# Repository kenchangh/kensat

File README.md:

# KENSAT — Edge-AI Compute in Orbit

> A 2U CubeSat that runs a large language model on-orbit. A power-gated NVIDIA
> Jetson Orin Nano executes neural-network inference in space, and the results
> are downlinked over a custom UHF radio link to amateur ground stations.

KENSAT's mission is to demonstrate **autonomous AI compute on a small
satellite** — taking a GPU-class accelerator and a quantized LLM out of the
data center and running them inside the tight power, thermal, and reliability
envelope of a 2U CubeSat. The on-board computer wakes the Jetson only when
needed, runs an inference within a measured energy budget, and frames the
output for downlink. Everything else in the spacecraft — the flight software,
the UHF radio and its RF matching networks, the power system, and the
antenna-deployment hardware — exists to get that compute on orbit, keep it
alive, and get its results to the ground.

**Why it's hard.** Edge AI in orbit means treating a multi-watt accelerator as
a scheduled, fault-tolerant *load*: powering it from a battery-backed bus only
in defined windows, dissipating its heat passively in vacuum, recovering it if
it hangs, and surviving the brownouts and resets that come with switching that
much current on a small satellite. KENSAT is built end to end around that
problem.

**Mission profile:** a 520 km sun-synchronous orbit, operating UHF amateur
radio at **437.08 MHz** for beaconing, telemetry downlink, and command uplink.
Telemetry — including downlinked inference results — is intentionally
**unencrypted** so amateur operators worldwide can receive and decode it.

---

## Radio link (for receiving stations)

KENSAT beacons openly on the UHF amateur band — no encryption, no keys.
Anyone with a 70 cm receiver and a G3RUH-capable TNC (Direwolf, gr-satellites,
SatNOGS) can decode it.

| | |
|---|---|
| **Beacon / downlink frequency** | **437.080 MHz** |
| **Transmitter** | Mode U — GFSK 1k2 AX.25 G3RUH |
| **Modulation** | GFSK |
| **Baud** | 1200 |
| **Framing** | AX.25 UI, NRZI + G3RUH |
| **Source callsign** | KO6IKZ |
| **Beacon interval** | ~10 s |
| **Status** | active |
| **Encryption** | none — telemetry is open by design |

Everything in the info field is plain ASCII. Frames are identified by their
first token:

| Frame | Carries |
|-------|---------|
| `BCN` | Housekeeping beacon: cumulative sequence number, boot count, reset cause, uptime, body rates, uplink frames received |
| `LLM` | One per on-orbit inference: Jetson temperatures and peaks, power, RAM, model-load and inference times, result CRC-32, and how many text frames to expect |
| `TXT` | The text the on-board LLM generated, as numbered chunks — `s=` result, `c=<k>/<m>` chunk, `h=` CRC-32 of the whole result |
| `ACK` | Acknowledgement of a received telecommand |

A result is sent one chunk per beacon cycle and the whole set twice, because
the link has no ARQ. To reassemble: group by `s=`, order by `c=`, concatenate,
and check `h=` (standard CRC-32). `ground-station/llm_downlink.py` does this
for you, from live decoder output or a saved log.

Command uplink is a short authenticated ASCII telecommand (Si4463 native
framing, CRC-16) that can inhibit the transmitter, ping the spacecraft, uplink
a prompt of up to 256 characters for the LLM in a single frame (which starts
the inference), or run a library prompt. Formats, verbs and the
reasoning behind them are in
**[firmware/obc/README.md](firmware/obc/README.md#the-radio-link)**.

Decoders, the result reassembler and an end-to-end test harness live in
**[ground-station](ground-station)**.

---

## System at a glance

```
        ┌──────────────────────────────────────────────┐
        │  Burn-Wire Board (custom)                     │  Slot 4 (top)
        │  Antenna-release driver · resistive heating   │
        ├──────────────────────────────────────────────┤
        │  Radio Board (custom)                         │  Slot 3
        │  Si4463 UHF transceiver + AS179 T/R switch    │
        │  Jetson Orin Nano (edge-AI payload)           │
        ├──────────────────────────────────────────────┤
        │  EPS Board (custom)                           │  Slot 2
        │  2S2P 18650 pack · rails · hardware watchdog  │
        ├──────────────────────────────────────────────┤
        │  Pumpkin MB + PPM D1 (PIC24FJ256GB210)        │  Slot 1 (bottom)
        │  OBC — always-on C&DH, Salvo RTOS             │
        └──────────────────────────────────────────────┘
              104-pin CubeSat Kit Bus (H1/H2)

   UHF dipole ── U.FL ── matching network ── AS179 ── Si4463 ── SPI ── PIC24
```

Boards interconnect over the 104-pin CubeSat Kit Bus. The PIC24 is the
always-on flight computer; it talks to the EPS over I²C, drives the Si4463
radio over SPI, controls and exchanges data with the Jetson over UART, and
fires the antenna-deployment burn wires over GPIO.

See **[docs/system-architecture.md](docs/system-architecture.md)** for the full
spec: pinouts, bus map, operational modes, deployment state machine, power
budget, and thermal analysis.

---

## Subsystems

| Subsystem | What it is | Highlights |
|-----------|-----------|------------|
| **[firmware/obc](firmware/obc)** | PIC24 flight software (C, Salvo RTOS) | Fault-tolerant antenna deployment with flash-persisted state, AX.25 beacons, Si4463 driver, IMU, SD/serial-flash logging, command parser |
| **[radio](radio)** | Custom 437 MHz UHF radio board | Si4463 + AS179 T/R switch, ESP32-S3 firmware, KiCad 2-layer design |
| **[radio/rf-design](radio/rf-design)** | RF matching-network design & test | Custom scikit-rf optimizer over LCSC-stocked parts, CPWG parasitic modeling, ADALM-Pluto SDR test bench |
| **[eps](eps)** | Electrical power system board | 2S2P 18650 pack, regulated rails, hardware watchdog (KiCad) |
| **[burnwire](burnwire)** | Antenna-release deployment board | Redundant nichrome burn-wire driver (KiCad) |
| **[jetson](jetson)** | Edge-AI payload | Jetson Orin Nano running a quantized LLM (llama.cpp/TinyLlama) over UART, systemd daemons, thermal management |
| **[ground-station](ground-station)** | SDR ground station & decoders | ADALM-Pluto RX/TX, AX.25 beacon decoder, DSP diagnostics, end-to-end test harness |
| **[docs](docs)** | System documentation | Architecture spec, radio guide, Jetson startup, debug notes |

---

## Engineering highlights

- **An LLM running in orbit.** The payload is an NVIDIA Jetson Orin Nano running
  a quantized TinyLlama model under llama.cpp. The always-on PIC24 keeps it
  powered down, then — on schedule or command — switches on its rail through a
  high-side load switch, waits for the Jetson to boot and signal `READY` over
  UART, dispatches a prompt, collects the generated text, powers the Jetson back
  off, and queues the result for downlink. The whole cycle is bounded by a
  measured **per-inference energy budget** so a single run can't drain the pack.
  Prompts come either from a library pre-loaded on the payload — so the mission
  produces results with no uplink at all — or from the ground, uplinked as a
  single 256-byte prompt field that the OBC runs as soon as it arrives.
  ([docs/system-architecture.md §6.2](docs/system-architecture.md), [jetson/](jetson))

- **Treating a GPU as a spacecraft load.** Running multi-watt edge compute on a
  2U bus is a systems problem: the EPS sizes a battery-backed rail and a
  hardware watchdog around the Jetson's draw, the OBC power-gates it and can
  recover a hung payload by cutting power, and the design accounts for
  dissipating its heat **passively in vacuum**, where there's no convection.
  ([docs/system-architecture.md §8.1](docs/system-architecture.md))

- **Fault-tolerant by construction.** Both the inference cycle and the antenna
  burn-wire release are one-shot, flash-persisted state machines that survive
  the brownouts and resets that come with switching large currents: attempt
  counts are written *before* energizing, success flags only *after* completion,
  and the RF-silence hold fails *safe* toward staying quiet.
  ([details](docs/system-architecture.md))

- **A complete UHF link to get results down.** TX / RX / antenna matching
  networks were designed with a custom scikit-rf grid-search optimizer that
  models PCB traces as CPWG transmission lines (elliptic-integral method) and
  snaps to real LCSC part values, then validated on an ADALM-Pluto SDR loopback
  bench (gain sweep, harmonics, insertion loss). Inference output is framed as
  AX.25 and downlinked openly. ([radio/rf-design](radio/rf-design))

- **Signal-integrity-aware bus design.** The Si4463 SPI bus crosses two
  board-to-board connectors; the design derates the clock and adds series
  termination accordingly. ([docs/spi-debug-notes.md](docs/spi-debug-notes.md))

---

## Repository layout

```
kensat/
├── docs/             System architecture spec + guides
├── firmware/obc/     PIC24 flight software (app/ + bsp/)
├── radio/            UHF radio: ESP32 firmware, KiCad board, RF design
├── eps/              Electrical power system board (KiCad)
├── burnwire/         Antenna deployment board (KiCad)
├── jetson/           Edge-AI payload daemon + systemd units
└── ground-station/   SDR scripts, beacon decoder, diagnostics
```

## Building

- **OBC firmware** depends on proprietary vendor SDKs (Pumpkin CubeSat Kit BSP,
  Salvo RTOS) that are **not** redistributed here. See
  **[firmware/obc/BUILD.md](firmware/obc/BUILD.md)**.
- **Radio firmware** builds with arduino-cli for the ESP32-S3.
- **RF design / ground-station** tools are Python; see the `requirements.txt`
  in each directory.

## License

Original work in this repository is released under the [MIT License](LICENSE).
Proprietary vendor SDKs the firmware builds against are **not** included and are
**not** covered by that license — see the LICENSE file and
[firmware/obc/BUILD.md](firmware/obc/BUILD.md).

---

*KENSAT — UHF amateur satellite, 437.08 MHz. Telemetry is open and unencrypted
by design, in the tradition of the amateur radio community.*

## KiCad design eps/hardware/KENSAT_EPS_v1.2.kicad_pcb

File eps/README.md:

# Electrical Power System (EPS)

Custom EPS board for KENSAT — Slot 2 in the 2U stack, above the OBC. Generates and
distributes the satellite's power rails, manages the battery pack, and provides
a hardware watchdog that can power-cycle the rest of the spacecraft.

- **Battery:** 2S2P 18650 Li-ion pack (mounted on the board underside)
- **Rails:** regulated buses distributed over the 104-pin CubeSat Kit Bus
- **Telemetry:** battery voltage / current / temperature, read by the OBC over I²C
- **Reliability:** hardware watchdog (see
  [docs/system-architecture.md](../docs/system-architecture.md) §7.1)

## Files

```
eps/hardware/
├── KENSAT_EPS_v1.2.kicad_pro   KiCad project
├── KENSAT_EPS_v1.2.kicad_sch   Schematic
└── KENSAT_EPS_v1.2.kicad_pcb   PCB layout
```

Open with [KiCad](https://www.kicad.org/) 7+. Power-rail and bus pin
assignments are documented in
[docs/system-architecture.md](../docs/system-architecture.md) §5.6–5.7.

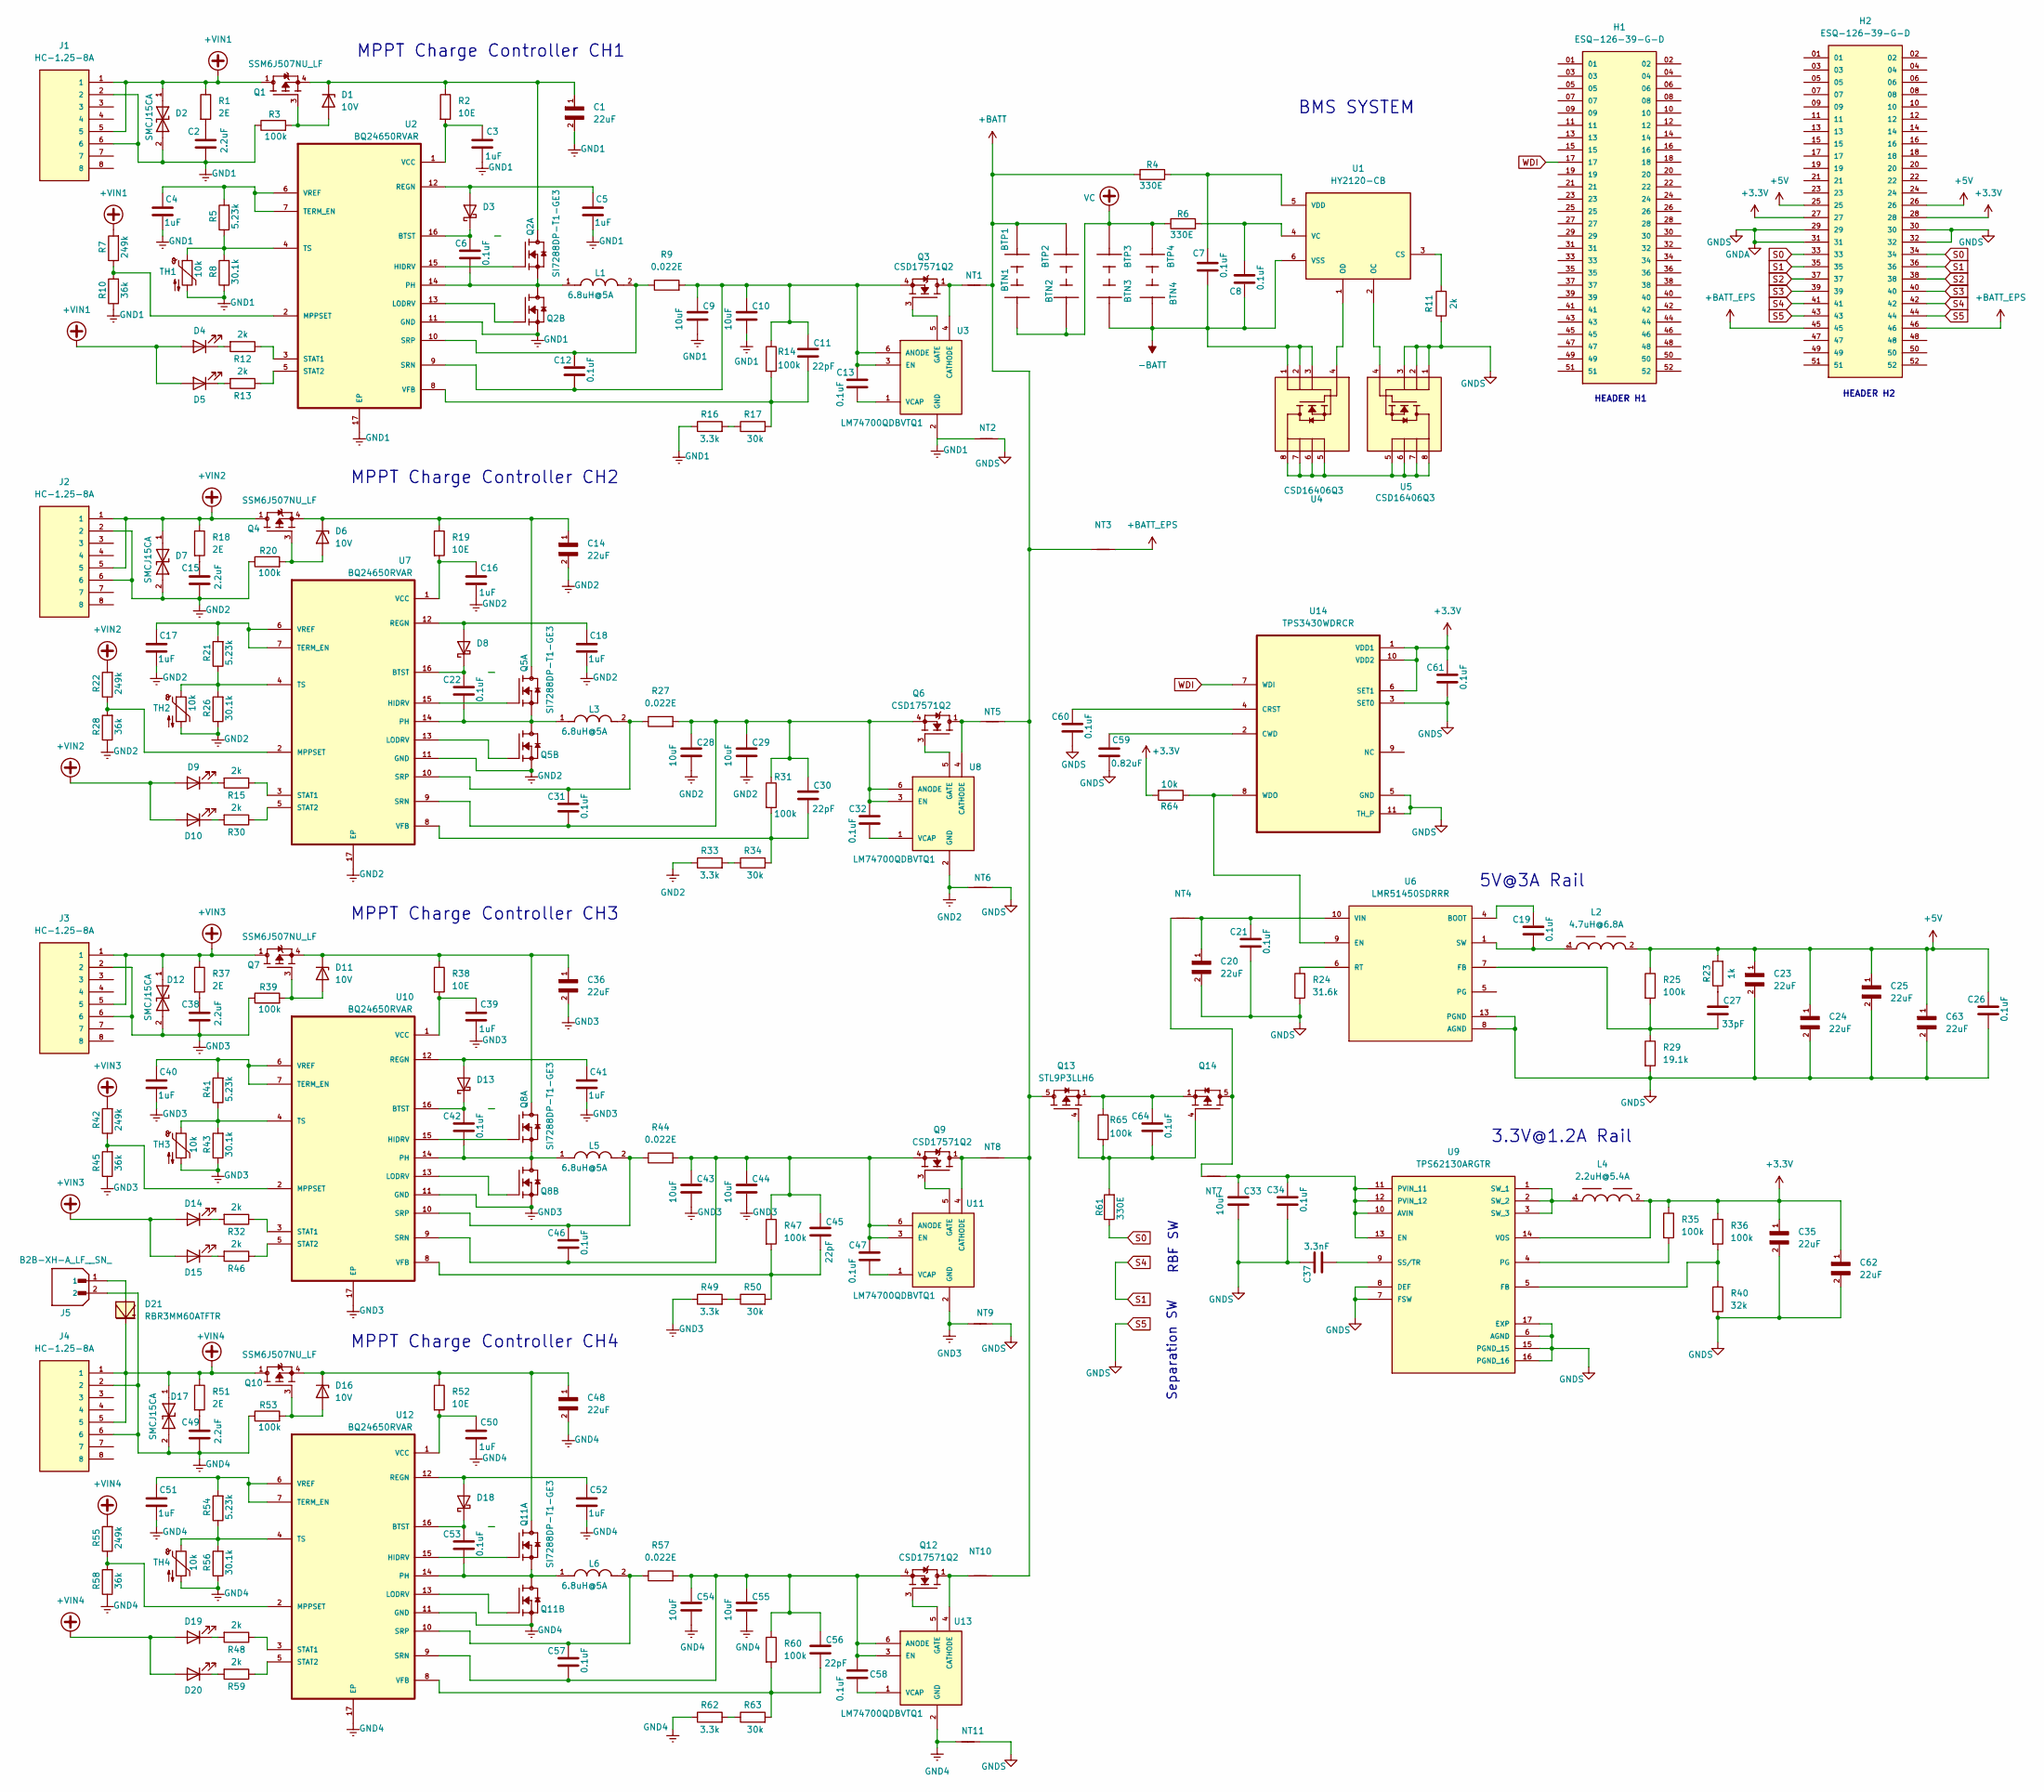
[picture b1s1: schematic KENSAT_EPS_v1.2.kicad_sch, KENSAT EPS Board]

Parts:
BTN1, BTN2, BTN3, BTN4: MY-18650-02; BAT_254TR; PARTREV C; LCSC Part C2979182
BTP1, BTP2, BTP3, BTP4: MY-18650-02; BAT_254TR; PARTREV C; LCSC Part C2979182
C1, C14, C20, C23, C24, C25, C35, C36, C48, C62, C63: 22uF; CAPC3225X270N; Voltage 35V; LCSC Part C386098
C2, C15, C38, C49: 2.2uF; C_1210_3225Metric; Voltage 100V; LCSC Part C92775
C3, C4, C5, C16, C17, C18, C39, C40, C41, C50, C51, C52: 1uF; C_0603_1608Metric; Voltage 35V; LCSC Part C841050
C6, C7, C8, C12, C13, C19, C21, C22, C26, C31, C32, C34, C42, C46, C47, C53, C57, C58, C60, C61, C64: 0.1uF; C_0603_1608Metric; Voltage 50V; LCSC Part C386155
C9, C10, C28, C29, C33, C43, C44, C54, C55: 10uF; C_1210_3225Metric; Voltage 35V; LCSC Part C2177081
C11, C30, C45, C56: 22pF; C_0603_1608Metric; Voltage 50V; LCSC Part C2169931
C27: 33pF; C_0603_1608Metric; Voltage 16V; LCSC Part C2169365
C37: 3.3nF; C_0603_1608Metric; Voltage 50V; LCSC Part C107088
C59: 0.82uF; C_0603_1608Metric; Voltage 25V; LCSC Part C5360807
D1, D6, D11, D16: 10V; D_SOD-123; LCSC Part C49435551
D2, D7, D12, D17: SMCJ15CA; DIOM7959X262N; PARTREV 11/20/15; LCSC Part C2842380
D3, D8, D13, D18: D_Schottky; D_SOD-323; LCSC Part C151503
D4, D9, D14, D19: LED; R_0603_1608Metric; LCSC Part C125099
D5, D10, D15, D20: LED; R_0603_1608Metric; LCSC Part C125093
D21: RBR3MM60ATFTR; SOD-123FL-2; LCSC Part C559758
H1, H2: ESQ-126-39-G-D; PARTREV R; LCSC Part C7466599
J1, J2, J3, J4: HC-1.25-8A; DF138P125DSA; MOUSER_PART_NUMBER 798-DF13-8P-1.25DSA
J5: B2B-XH-A_LF__SN_; JST_B2B-XH-A_LF__SN_; PARTREV N/A; LCSC Part C158012
L1, L3, L5, L6: 6.8uH@5A; INDDFN420X420X420-2N; PARTREV 09/15/2025; LCSC Part C52988778
L2: 4.7uH@6.8A; WE-XHMI_5030; LCSC Part C50326272
L4: 2.2uH@5.4A; WE-XHMI_5030; LCSC Part C48391578
NT1, NT2, NT3, NT4, NT5, NT6, NT7, NT8, NT9, NT10, NT11: NetTie_2; SolderJumper-2_P1.3mm_Bridged2Bar_Pad1.0x2.5mm
Q1, Q4, Q7, Q10: SSM6J507NU_LF; TRANS_SSM6J507NU_LF; PARTREV 2.0; LCSC Part C146318
Q2, Q5, Q8, Q11: SI7288DP-T1-GE3; TRANS_SI7288DP-T1-GE3; PARTREV A; LCSC Part C126988
Q3, Q6, Q9, Q12: CSD17571Q2; TRANS_CSD17571Q2; PARTREV A; LCSC Part C962382
Q13, Q14: STL9P3LLH6; TRANS_STL9P3LLH6; PARTREV 3; LCSC Part C2969828
R1, R18, R37, R51: 2E; R_2010_5025Metric; LCSC Part C2084800
R2, R19, R38, R52: 10E; R_1206_3216Metric; LCSC Part C304131
R3, R14, R20, R25, R31, R35, R36, R39, R47, R53, R60, R65: 100k; R_0603_1608Metric; LCSC Part C163504
R4, R6, R61: 330E; R_1206_3216Metric; LCSC Part C114944
R5, R21, R41, R54: 5.23k; R_0603_1608Metric; LCSC Part C185317
R7, R22, R42, R55: 249k; R_0603_1608Metric; LCSC Part C311921
R8, R26, R43, R56: 30.1k; R_0603_1608Metric; LCSC Part C137745
R9, R27, R44, R57: 0.022E; R_1206_3216Metric; LCSC Part C875620
R10, R28, R45, R58: 36k; R_0603_1608Metric; LCSC Part C311904
R11, R12, R13, R15, R30, R32, R46, R48, R59: 2k; R_0603_1608Metric; LCSC Part C105576
R16, R33, R49, R62: 3.3k; R_0603_1608Metric; LCSC Part C227493
R17, R34, R50, R63: 30k; R_0603_1608Metric; LCSC Part C700503
R23: 1k; R_1206_3216Metric; LCSC Part C131398
R24: 31.6k; R_0603_1608Metric; LCSC Part C185339
R29: 19.1k; R_0603_1608Metric; LCSC Part C173754
R40: 32k; R_0603_1608Metric; LCSC Part C861325
R64: 10k; R_0603_1608Metric; LCSC Part C98220
TH1, TH2, TH3, TH4: 10k; PinHeader_1x02_P2.00mm_Vertical; LCSC Part C7509625
U1: HY2120-CB; SOT-23-6; PARTREV 1.5_00; LCSC Part C116509
U2, U7, U10, U12: BQ24650RVAR; QFN50P350X350X100-17N; LCSC Part C53712
U3, U8, U11, U13: LM74700QDBVTQ1; SOT95P280X145-6N; PARTREV F; LCSC Part C2653623
U4, U5: CSD16406Q3; TRANS_CSD16406Q3; LCSC Part C2861720
U6: LMR51450SDRRR; CONV_LMR51450SDRRR; PARTREV December 2022; LCSC Part C6890985
U9: TPS62130ARGTR; QFN50P300X300X100-17N; PARTREV E; LCSC Part C337502
U14: TPS3430WDRCR; VREG_V62_16624-01YE; LCSC Part C2870545

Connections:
+3.3V: C35.1, C61.2, C62.1, H2.27, H2.28, L4.2, R35.1, R36.1, R64.2, U9.14 (VOS), U14.1 (VDD1), U14.6 (SET1), U14.10 (VDD2)
+5V: C23.1, C24.1, C25.1, C26.2, C63.1, H2.25, H2.26, L2.2, R23.2, R25.1
+BATT: BTP1.P1, BTP1.P2, BTP2.P1, BTP2.P2, NT1.2, NT3.1, NT5.2, NT8.2, NT10.2, Q13.5, Q13.5_1, Q13.5_2, R4.1
+BATT_EPS: H2.45, H2.46, NT3.2
+VIN1: D2.1, D4.2 (A), D5.2 (A), J1.1, J1.5, Q1.1, Q1.2, Q1.5, Q1.6, Q1.7, R1.1, R7.2
+VIN2: D7.1, D9.2 (A), D10.2 (A), J2.1, J2.5, Q4.1, Q4.2, Q4.5, Q4.6, Q4.7, R18.1, R22.2
+VIN3: D12.1, D14.2 (A), D15.2 (A), J3.1, J3.5, Q7.1, Q7.2, Q7.5, Q7.6, Q7.7, R37.1, R42.2
+VIN4: D17.1, D19.2 (A), D20.2 (A), D21.C, J4.1, J4.5, Q10.1, Q10.2, Q10.5, Q10.6, Q10.7, R51.1, R55.2
-BATT: BTN3.P1, BTN3.P2, BTN4.P1, BTN4.P2, C7.1, C8.1, U1.6 (VSS), U4.1, U4.2, U4.3
GND1: C1.2, C2.2, C3.2, C4.2, C5.2, C9.2, C10.2, D2.2, J1.2, J1.6, NT2.1, Q2.3, R3.1, R8.1, R10.1, R16.1, TH1.2, U2.11 (GND), U2.17 (EP), U3.2 (GND)
GND2: C14.2, C15.2, C16.2, C17.2, C18.2, C28.2, C29.2, D7.2, J2.2, J2.6, NT6.1, Q5.3, R20.1, R26.1, R28.1, R33.1, TH2.2, U7.11 (GND), U7.17 (EP), U8.2 (GND)
GND3: C36.2, C38.2, C39.2, C40.2, C41.2, C43.2, C44.2, D12.2, J3.2, J3.6, NT9.1, Q8.3, R39.1, R43.1, R45.1, R49.1, TH3.2, U10.11 (GND), U10.17 (EP), U11.2 (GND)
GND4: C48.2, C49.2, C50.2, C51.2, C52.2, C54.2, C55.2, D17.2, J4.2, J4.6, J5.2, NT11.1, Q11.3, R53.1, R56.1, R58.1, R62.1, TH4.2, U12.11 (GND), U12.17 (EP), U13.2 (GND)
unnamed: C2.1, R1.2
unnamed: C15.1, R18.2
unnamed: C19.1, L2.1, U6.1 (SW), U6.2 (SW), U6.3 (SW)
unnamed: C20.1, C21.2, NT4.2, U6.10 (VIN), U6.11 (VIN), U6.12 (VIN)
unnamed: C27.1, R23.1
unnamed: C38.1, R37.2
unnamed: C49.1, R51.2
unnamed: C64.1, Q13.4, Q14.4, R61.2, R65.2
unnamed: C64.2, Q13.1, Q13.2, Q13.3, Q14.1, Q14.2, Q14.3, R65.1
unnamed: D1.2 (A), Q1.3, R3.2
unnamed: C1.1, D1.1 (K), Q1.4, Q1.8, Q2.7_8_9, R2.1
unnamed: C5.1, D3.2 (A), U2.12 (REGN)
unnamed: C6.2, D3.1 (K), U2.16 (BTST)
unnamed: D4.1 (K), R12.2
unnamed: D5.1 (K), R13.2
unnamed: D6.2 (A), Q4.3, R20.2
unnamed: C14.1, D6.1 (K), Q4.4, Q4.8, Q5.7_8_9, R19.1
unnamed: C18.1, D8.2 (A), U7.12 (REGN)
unnamed: C22.2, D8.1 (K), U7.16 (BTST)
unnamed: D9.1 (K), R15.2
unnamed: D10.1 (K), R30.2
unnamed: D11.2 (A), Q7.3, R39.2
unnamed: C36.1, D11.1 (K), Q7.4, Q7.8, Q8.7_8_9, R38.1
unnamed: C41.1, D13.2 (A), U10.12 (REGN)
unnamed: C42.2, D13.1 (K), U10.16 (BTST)
unnamed: D14.1 (K), R32.2
unnamed: D15.1 (K), R46.2
unnamed: D16.2 (A), Q10.3, R53.2
unnamed: C48.1, D16.1 (K), Q10.4, Q10.8, Q11.7_8_9, R52.1
unnamed: C52.1, D18.2 (A), U12.12 (REGN)
unnamed: C53.2, D18.1 (K), U12.16 (BTST)
unnamed: D19.1 (K), R48.2
unnamed: D20.1 (K), R59.2
unnamed: D21.A, J5.1
unnamed: NT4.1, NT7.1, Q14.5, Q14.5_1, Q14.5_2
unnamed: R16.2, R17.1
unnamed: R33.2, R34.1
unnamed: R49.2, R50.1
unnamed: R62.2, R63.1
unnamed: R11.2, U1.3 (CS)
unnamed: U1.2 (OC), U5.4
unnamed: U1.1 (OD), U4.4
unnamed: C8.2, R6.2, U1.4 (VC)
unnamed: C7.2, R4.2, U1.5 (VDD)
unnamed: Q2.2, U2.15 (HIDRV)
unnamed: Q2.4, U2.13 (LODRV)
unnamed: R7.1, R10.2, U2.2 (MPPSET)
unnamed: C6.1, L1.1, Q2.1, Q2.5_6_10, U2.14 (PH)
unnamed: C9.1, C10.1, C11.1, C12.1, C13.2, Q3.4, Q3.8, R9.2, R14.1, U2.9 (SRN), U3.3 (EN), U3.6 (ANODE)
unnamed: C12.2, L1.2, R9.1, U2.10 (SRP)
unnamed: R12.1, U2.3 (STAT1)
unnamed: R13.1, U2.5 (STAT2)
unnamed: C4.1, R5.2, U2.6 (VREF), U2.7 (TERM_EN)
unnamed: R5.1, R8.2, TH1.1, U2.4 (TS)
unnamed: C3.1, R2.2, U2.1 (VCC)
unnamed: C11.2, R14.2, R17.2, U2.8 (VFB)
unnamed: NT1.1, Q3.1, Q3.2, Q3.5, Q3.6, Q3.7, U3.4 (CATHODE)
unnamed: Q3.3, U3.5 (GATE)
unnamed: C13.1, U3.1 (VCAP)
unnamed: U4.5, U4.6, U4.7, U4.8, U5.5, U5.6, U5.7, U5.8
unnamed: C19.2, U6.4 (BOOT)
unnamed: C27.2, R25.2, R29.1, U6.7 (FB)
unnamed: R24.1, U6.6 (RT)
unnamed: Q5.2, U7.15 (HIDRV)
unnamed: Q5.4, U7.13 (LODRV)
unnamed: R22.1, R28.2, U7.2 (MPPSET)
unnamed: C22.1, L3.1, Q5.1, Q5.5_6_10, U7.14 (PH)
unnamed: C28.1, C29.1, C30.1, C31.1, C32.2, Q6.4, Q6.8, R27.2, R31.1, U7.9 (SRN), U8.3 (EN), U8.6 (ANODE)
unnamed: C31.2, L3.2, R27.1, U7.10 (SRP)
unnamed: R15.1, U7.3 (STAT1)
unnamed: R30.1, U7.5 (STAT2)
unnamed: C17.1, R21.2, U7.6 (VREF), U7.7 (TERM_EN)
unnamed: R21.1, R26.2, TH2.1, U7.4 (TS)
unnamed: C16.1, R19.2, U7.1 (VCC)
unnamed: C30.2, R31.2, R34.2, U7.8 (VFB)
unnamed: NT5.1, Q6.1, Q6.2, Q6.5, Q6.6, Q6.7, U8.4 (CATHODE)
unnamed: Q6.3, U8.5 (GATE)
unnamed: C32.1, U8.1 (VCAP)
unnamed: C33.1, C34.2, NT7.2, U9.10 (AVIN), U9.11 (PVIN_11), U9.12 (PVIN_12), U9.13 (EN)
unnamed: R36.2, R40.1, U9.5 (FB)
unnamed: R35.2, U9.4 (PG)
unnamed: C37.1, U9.9 (SS/TR)
unnamed: L4.1, U9.1 (SW_1), U9.2 (SW_2), U9.3 (SW_3)
unnamed: Q8.2, U10.15 (HIDRV)
unnamed: Q8.4, U10.13 (LODRV)
unnamed: R42.1, R45.2, U10.2 (MPPSET)
unnamed: C42.1, L5.1, Q8.1, Q8.5_6_10, U10.14 (PH)
unnamed: C43.1, C44.1, C45.1, C46.1, C47.2, Q9.4, Q9.8, R44.2, R47.1, U10.9 (SRN), U11.3 (EN), U11.6 (ANODE)
unnamed: C46.2, L5.2, R44.1, U10.10 (SRP)
unnamed: R32.1, U10.3 (STAT1)
unnamed: R46.1, U10.5 (STAT2)
unnamed: C40.1, R41.2, U10.6 (VREF), U10.7 (TERM_EN)
unnamed: R41.1, R43.2, TH3.1, U10.4 (TS)
unnamed: C39.1, R38.2, U10.1 (VCC)
unnamed: C45.2, R47.2, R50.2, U10.8 (VFB)
unnamed: NT8.1, Q9.1, Q9.2, Q9.5, Q9.6, Q9.7, U11.4 (CATHODE)
unnamed: Q9.3, U11.5 (GATE)
unnamed: C47.1, U11.1 (VCAP)
unnamed: Q11.2, U12.15 (HIDRV)
unnamed: Q11.4, U12.13 (LODRV)
unnamed: R55.1, R58.2, U12.2 (MPPSET)
unnamed: C53.1, L6.1, Q11.1, Q11.5_6_10, U12.14 (PH)
unnamed: C54.1, C55.1, C56.1, C57.1, C58.2, Q12.4, Q12.8, R57.2, R60.1, U12.9 (SRN), U13.3 (EN), U13.6 (ANODE)
unnamed: C57.2, L6.2, R57.1, U12.10 (SRP)
unnamed: R48.1, U12.3 (STAT1)
unnamed: R59.1, U12.5 (STAT2)
unnamed: C51.1, R54.2, U12.6 (VREF), U12.7 (TERM_EN)
unnamed: R54.1, R56.2, TH4.1, U12.4 (TS)
unnamed: C50.1, R52.2, U12.1 (VCC)
unnamed: C56.2, R60.2, R63.2, U12.8 (VFB)
unnamed: NT10.1, Q12.1, Q12.2, Q12.5, Q12.6, Q12.7, U13.4 (CATHODE)
unnamed: Q12.3, U13.5 (GATE)
unnamed: C58.1, U13.1 (VCAP)
unnamed: C60.2, U14.4 (CRST)
unnamed: C59.1, U14.2 (CWD)
unnamed: R64.1, U6.9 (EN), U14.8 (WDO)
S0: H2.33, H2.34, R61.1
S1: H2.35, H2.36, H2.41, H2.42
S2: H2.37, H2.38
S3: H2.39, H2.40
S5: C20.2, C21.1, C23.2, C24.2, C25.2, C26.1, C33.2, C34.1, C35.2, C37.2, C59.2, C60.1, C61.1, C62.2, C63.2, H2.29, H2.30, H2.31, H2.32, H2.43, H2.44, NT2.2, NT6.2, NT9.2, NT11.2, R11.1, R24.2, R29.2, R40.2, U5.1, U5.2, U5.3, U6.8 (AGND), U6.13 (PGND), U9.6 (AGND), U9.7 (FSW), U9.8 (DEF), U9.15 (PGND_15), U9.16 (PGND_16), U9.17 (EXP), U14.3 (SET0), U14.5 (GND), U14.11 (TH_P)
VC: BTN1.P1, BTN1.P2, BTN2.P1, BTN2.P2, BTP3.P1, BTP3.P2, BTP4.P1, BTP4.P2, R6.1
WDI: H1.17 (17_17), U14.7 (WDI)

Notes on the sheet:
MPPT Charge Controller CH3
MPPT Charge Controller CH4
MPPT Charge Controller CH1
HEADER H1
RBF SW
Separation SW
BMS SYSTEM
3.3V@1.2A Rail
MPPT Charge Controller CH2
HEADER H2
5V@3A Rail

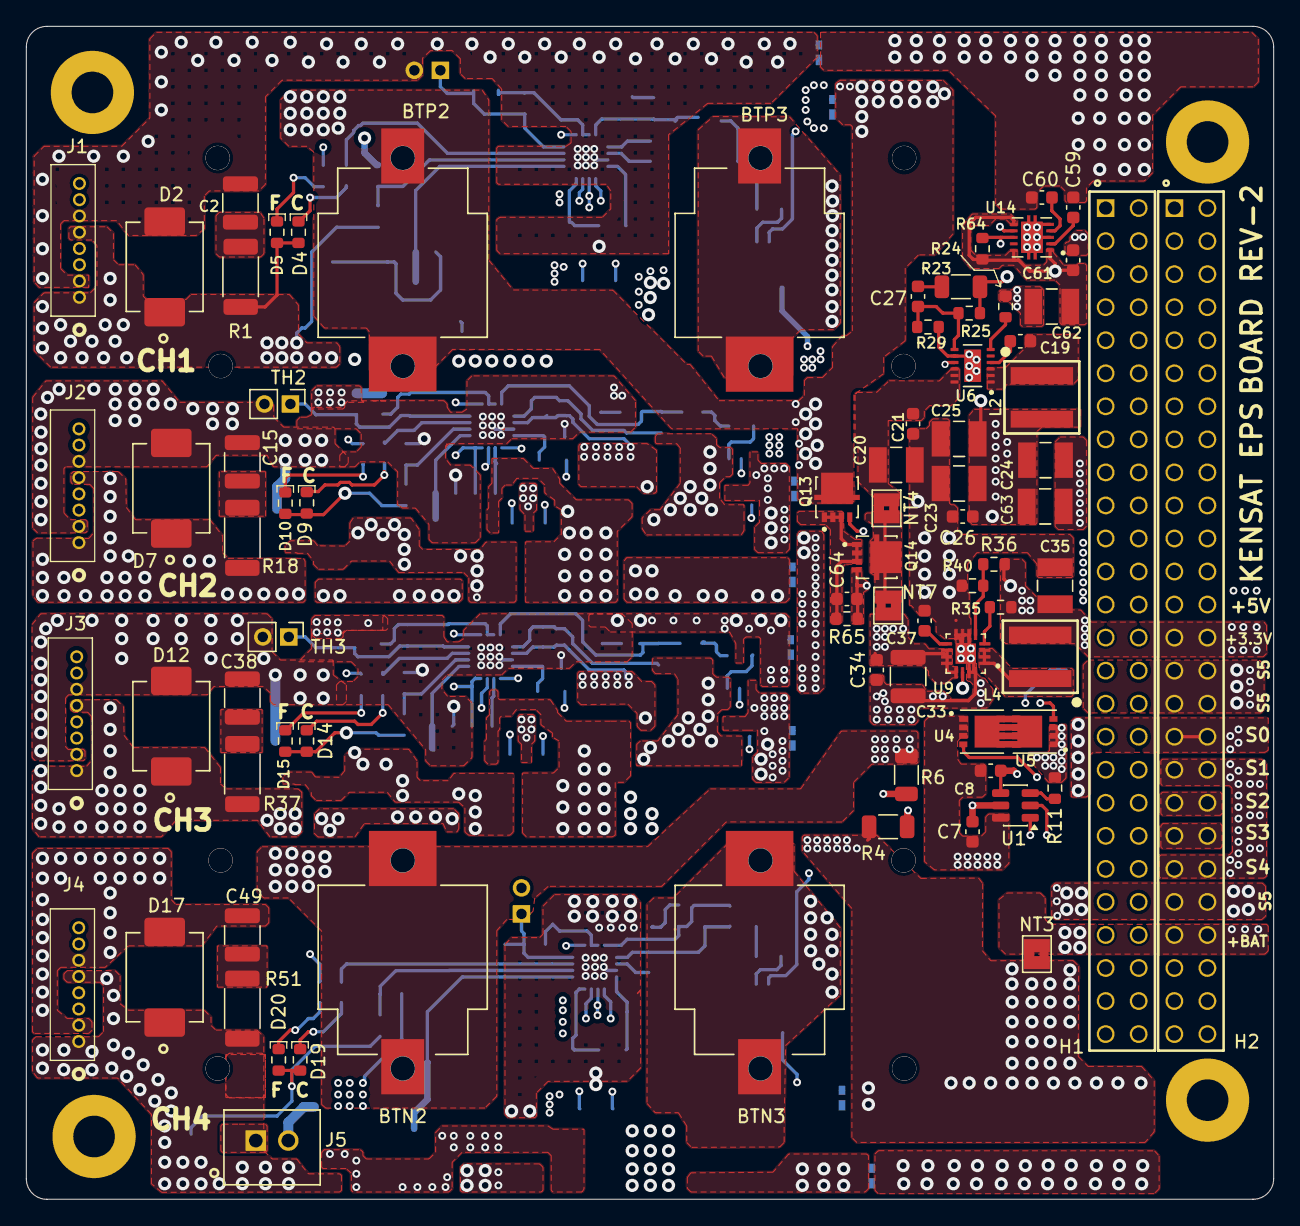
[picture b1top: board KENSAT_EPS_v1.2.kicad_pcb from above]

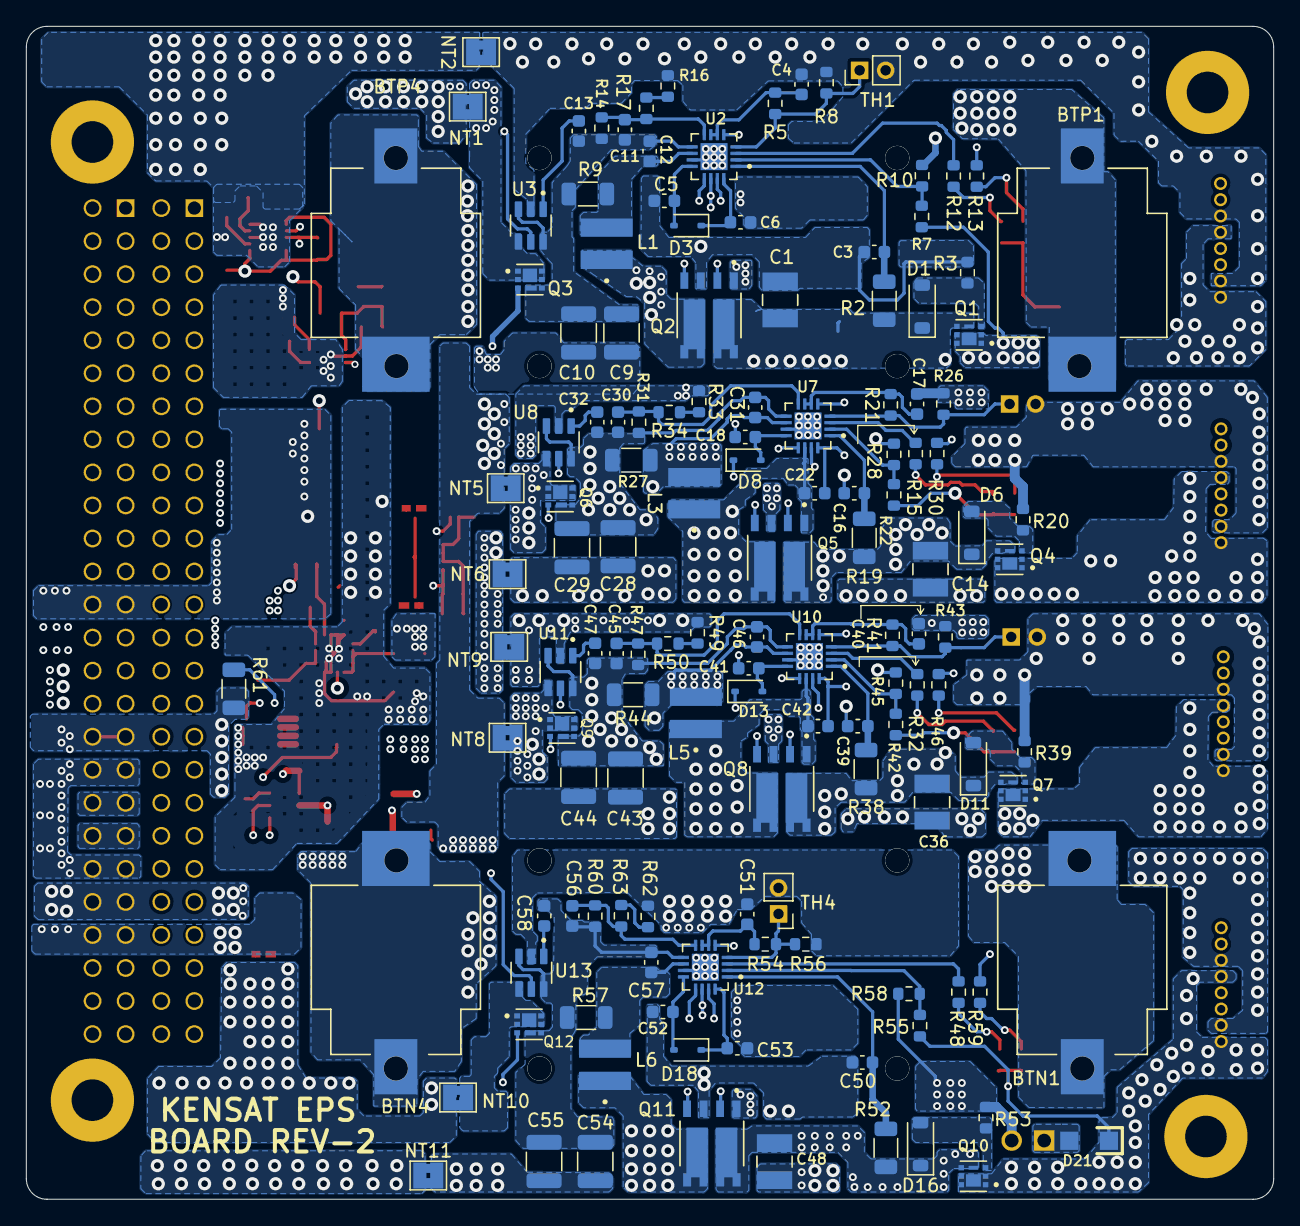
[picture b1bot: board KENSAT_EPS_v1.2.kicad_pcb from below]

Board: 4 copper layers, 95.9 x 90.2 mm, 214 parts (136 on the bottom side), 136 nets.

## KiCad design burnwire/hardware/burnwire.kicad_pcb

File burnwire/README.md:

# Burn-Wire Deployment Board

Antenna-release board for KENSAT — **Slot 4, the top board in the 2U stack**.
On command from the OBC, it drives **redundant resistive heating elements**
(nichrome burn wires) that melt through the fishing-line tether restraining the
tape-measure dipole; the elements then spring outward into a straight half-wave
dipole.

The release is driven by GPIO **IO.24** and **IO.25** from the PIC24, doubled
for redundancy, held HIGH for ~10 s. The deployment sequence — including the
flash-persisted, fail-safe, bounded-retry state machine — is documented in
[docs/system-architecture.md](../docs/system-architecture.md) §2.1–2.2 and
implemented in [firmware/obc/app/task_beacon.c](../firmware/obc/app/task_beacon.c).

## Files

```
burnwire/hardware/
└── burnwire.kicad_pro / .kicad_sch / .kicad_pcb   KiCad design
```

Open with [KiCad](https://www.kicad.org/) 7+.

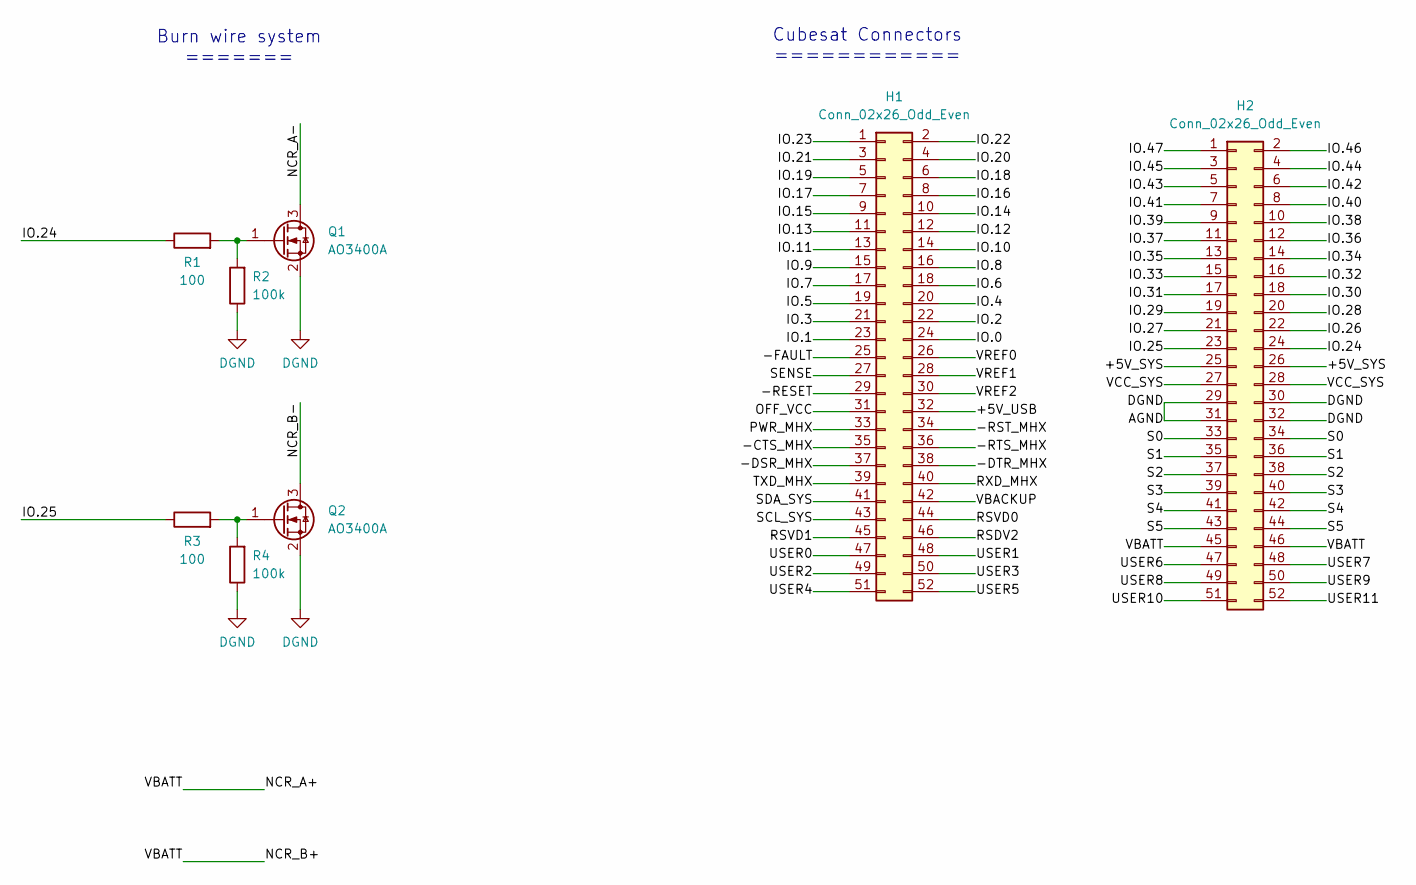
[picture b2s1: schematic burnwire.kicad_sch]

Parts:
H1, H2: Conn_02x26_Odd_Even; PinSocket_2x26_P2.54mm_Vertical
Q1, Q2: AO3400A; SOT-23
R1, R3: 100; R_Axial_DIN0207_L6.3mm_D2.5mm_P10.16mm_Horizontal
R2, R4: 100k; R_Axial_DIN0207_L6.3mm_D2.5mm_P10.16mm_Horizontal

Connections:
/+5V_SYS: H2.25, H2.26
/+5V_USB: H1.32
/-CTS_MHX: H1.35
/-DSR_MHX: H1.37
/-DTR_MHX: H1.38
/-FAULT: H1.25
/-RESET: H1.29
/-RST_MHX: H1.34
/-RTS_MHX: H1.36
/IO.0: H1.24
/IO.1: H1.23
/IO.2: H1.22
/IO.3: H1.21
/IO.4: H1.20
/IO.5: H1.19
/IO.6: H1.18
/IO.7: H1.17
/IO.8: H1.16
/IO.9: H1.15
/IO.10: H1.14
/IO.11: H1.13
/IO.12: H1.12
/IO.13: H1.11
/IO.14: H1.10
/IO.15: H1.9
/IO.16: H1.8
/IO.17: H1.7
/IO.18: H1.6
/IO.19: H1.5
/IO.20: H1.4
/IO.21: H1.3
/IO.22: H1.2
/IO.23: H1.1
/IO.24: H2.24, R1.1
/IO.25: H2.23, R3.1
/IO.26: H2.22
/IO.27: H2.21
/IO.28: H2.20
/IO.29: H2.19
/IO.30: H2.18
/IO.31: H2.17
/IO.32: H2.16
/IO.33: H2.15
/IO.34: H2.14
/IO.35: H2.13
/IO.36: H2.12
/IO.37: H2.11
/IO.38: H2.10
/IO.39: H2.9
/IO.40: H2.8
/IO.41: H2.7
/IO.42: H2.6
/IO.43: H2.5
/IO.44: H2.4
/IO.45: H2.3
/IO.46: H2.2
/IO.47: H2.1
/NCR_A-: Q1.3 (D)
/NCR_B-: Q2.3 (D)
/OFF_VCC: H1.31
/PWR_MHX: H1.33
/RSDV2: H1.46
/RSVD0: H1.44
/RSVD1: H1.45
/RXD_MHX: H1.40
/S0: H2.33, H2.34
/S1: H2.35, H2.36
/S2: H2.37, H2.38
/S3: H2.39, H2.40
/S4: H2.41, H2.42
/S5: H2.43, H2.44
/SCL_SYS: H1.43
/SDA_SYS: H1.41
/SENSE: H1.27
/TXD_MHX: H1.39
/USER0: H1.47
/USER1: H1.48
/USER2: H1.49
/USER3: H1.50
/USER4: H1.51
/USER5: H1.52
/USER6: H2.47
/USER7: H2.48
/USER8: H2.49
/USER9: H2.50
/USER10: H2.51
/USER11: H2.52
/VBACKUP: H1.42
/VBATT: H2.45, H2.46
/VCC_SYS: H2.27, H2.28
/VREF0: H1.26
/VREF1: H1.28
/VREF2: H1.30
DGND: H2.29, H2.30, H2.31, H2.32, Q1.2 (S), Q2.2 (S), R2.1, R4.1
unnamed: Q1.1 (G), R1.2, R2.2
unnamed: Q2.1 (G), R3.2, R4.2

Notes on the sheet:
Burn wire system =======
Cubesat Connectors ============
